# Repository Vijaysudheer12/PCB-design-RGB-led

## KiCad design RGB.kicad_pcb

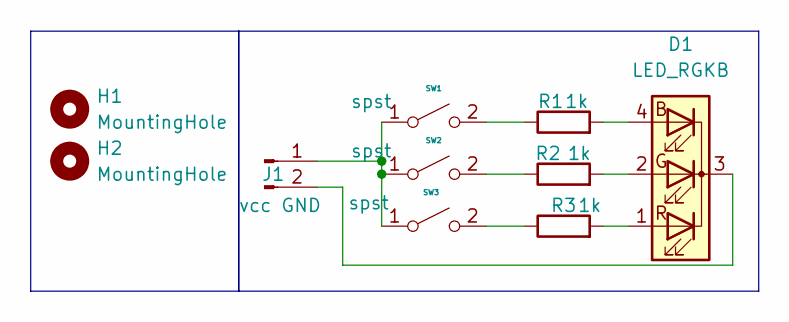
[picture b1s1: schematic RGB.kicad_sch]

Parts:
D1: LED_RGKB; LED_Kingbright_APFA3010_3x1.5mm_Horizontal
H1, H2: MountingHole; MountingHole_2.1mm
J1: vcc GND; PinHeader_1x02_P1.00mm_Horizontal
R1, R2, R3: 1k; R_0805_2012Metric
SW1, SW2, SW3: spst; SW_SPDT_PCM12

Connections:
unnamed: D1.4 (BA), R1.2
unnamed: D1.2 (GA), R2.2
unnamed: D1.3 (K), J1.2
unnamed: D1.1 (RA), R3.2
unnamed: J1.1, SW1.1 (A), SW2.1 (A), SW3.1 (A)
unnamed: R1.1, SW1.2 (B)
unnamed: R2.1, SW2.2 (B)
unnamed: R3.1, SW3.2 (B)

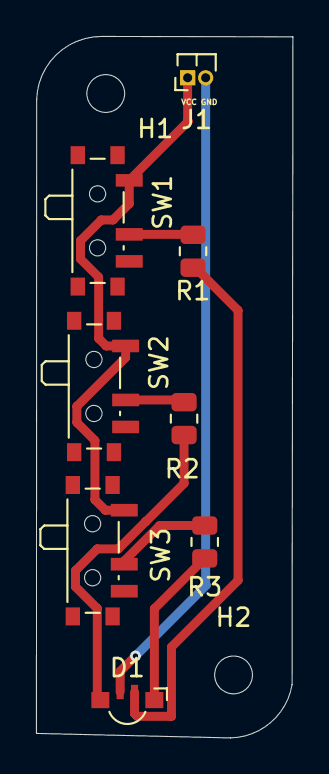
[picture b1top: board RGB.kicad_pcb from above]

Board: 2 copper layers, 14.2 x 39.0 mm, 10 parts (0 on the bottom side), 8 nets.
